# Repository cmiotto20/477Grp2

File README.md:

# 477Grp2
MOUSE is a mobile surveillance robot intended for indoor use, in corporate office or residential environments. MOUSE will be powered by four motors, each controlling its own wheel for mobility. There will be a large 12V battery allowing MOUSE to perform surveillance overnight without needing to have its battery replaced. When the battery does die, it will need to be recharged manually. MOUSE will have the ability for the motors to have variable speed control through the use of PWM signals. MOUSE will also have a custom circuit to step down the 12V from the battery to 5V for motors, sensors and ICs, aswell as 5V to 3.3V for the microprocessor.

To complete its surveillance functionality, MOUSE will have ultrasonic sensors on all four sides, allowing for the detection of movement. While stationary, MOUSE will use these sensors to detect any movement in its vicinity. Finally, there will be a viewable UI on a webpage to use MOUSE movement controls and display if any objects have been detected. MOUSE and the web interface will send data wirelessly through WiFi via a web server. The block diagram below represents the connections between the described functional components of MOUSE.

Additionally, we have the following stretch goals for the functionality of MOUSE. Mouse may have a series of LEDs which will be used to display diagnostics such as battery life. There may be an ability to measure data from a lidar sensor to provide redundancy and confirm the readings from the ultrasonic sensors. Finally, MOUSE may be able to follow a predetermined path set by the user.

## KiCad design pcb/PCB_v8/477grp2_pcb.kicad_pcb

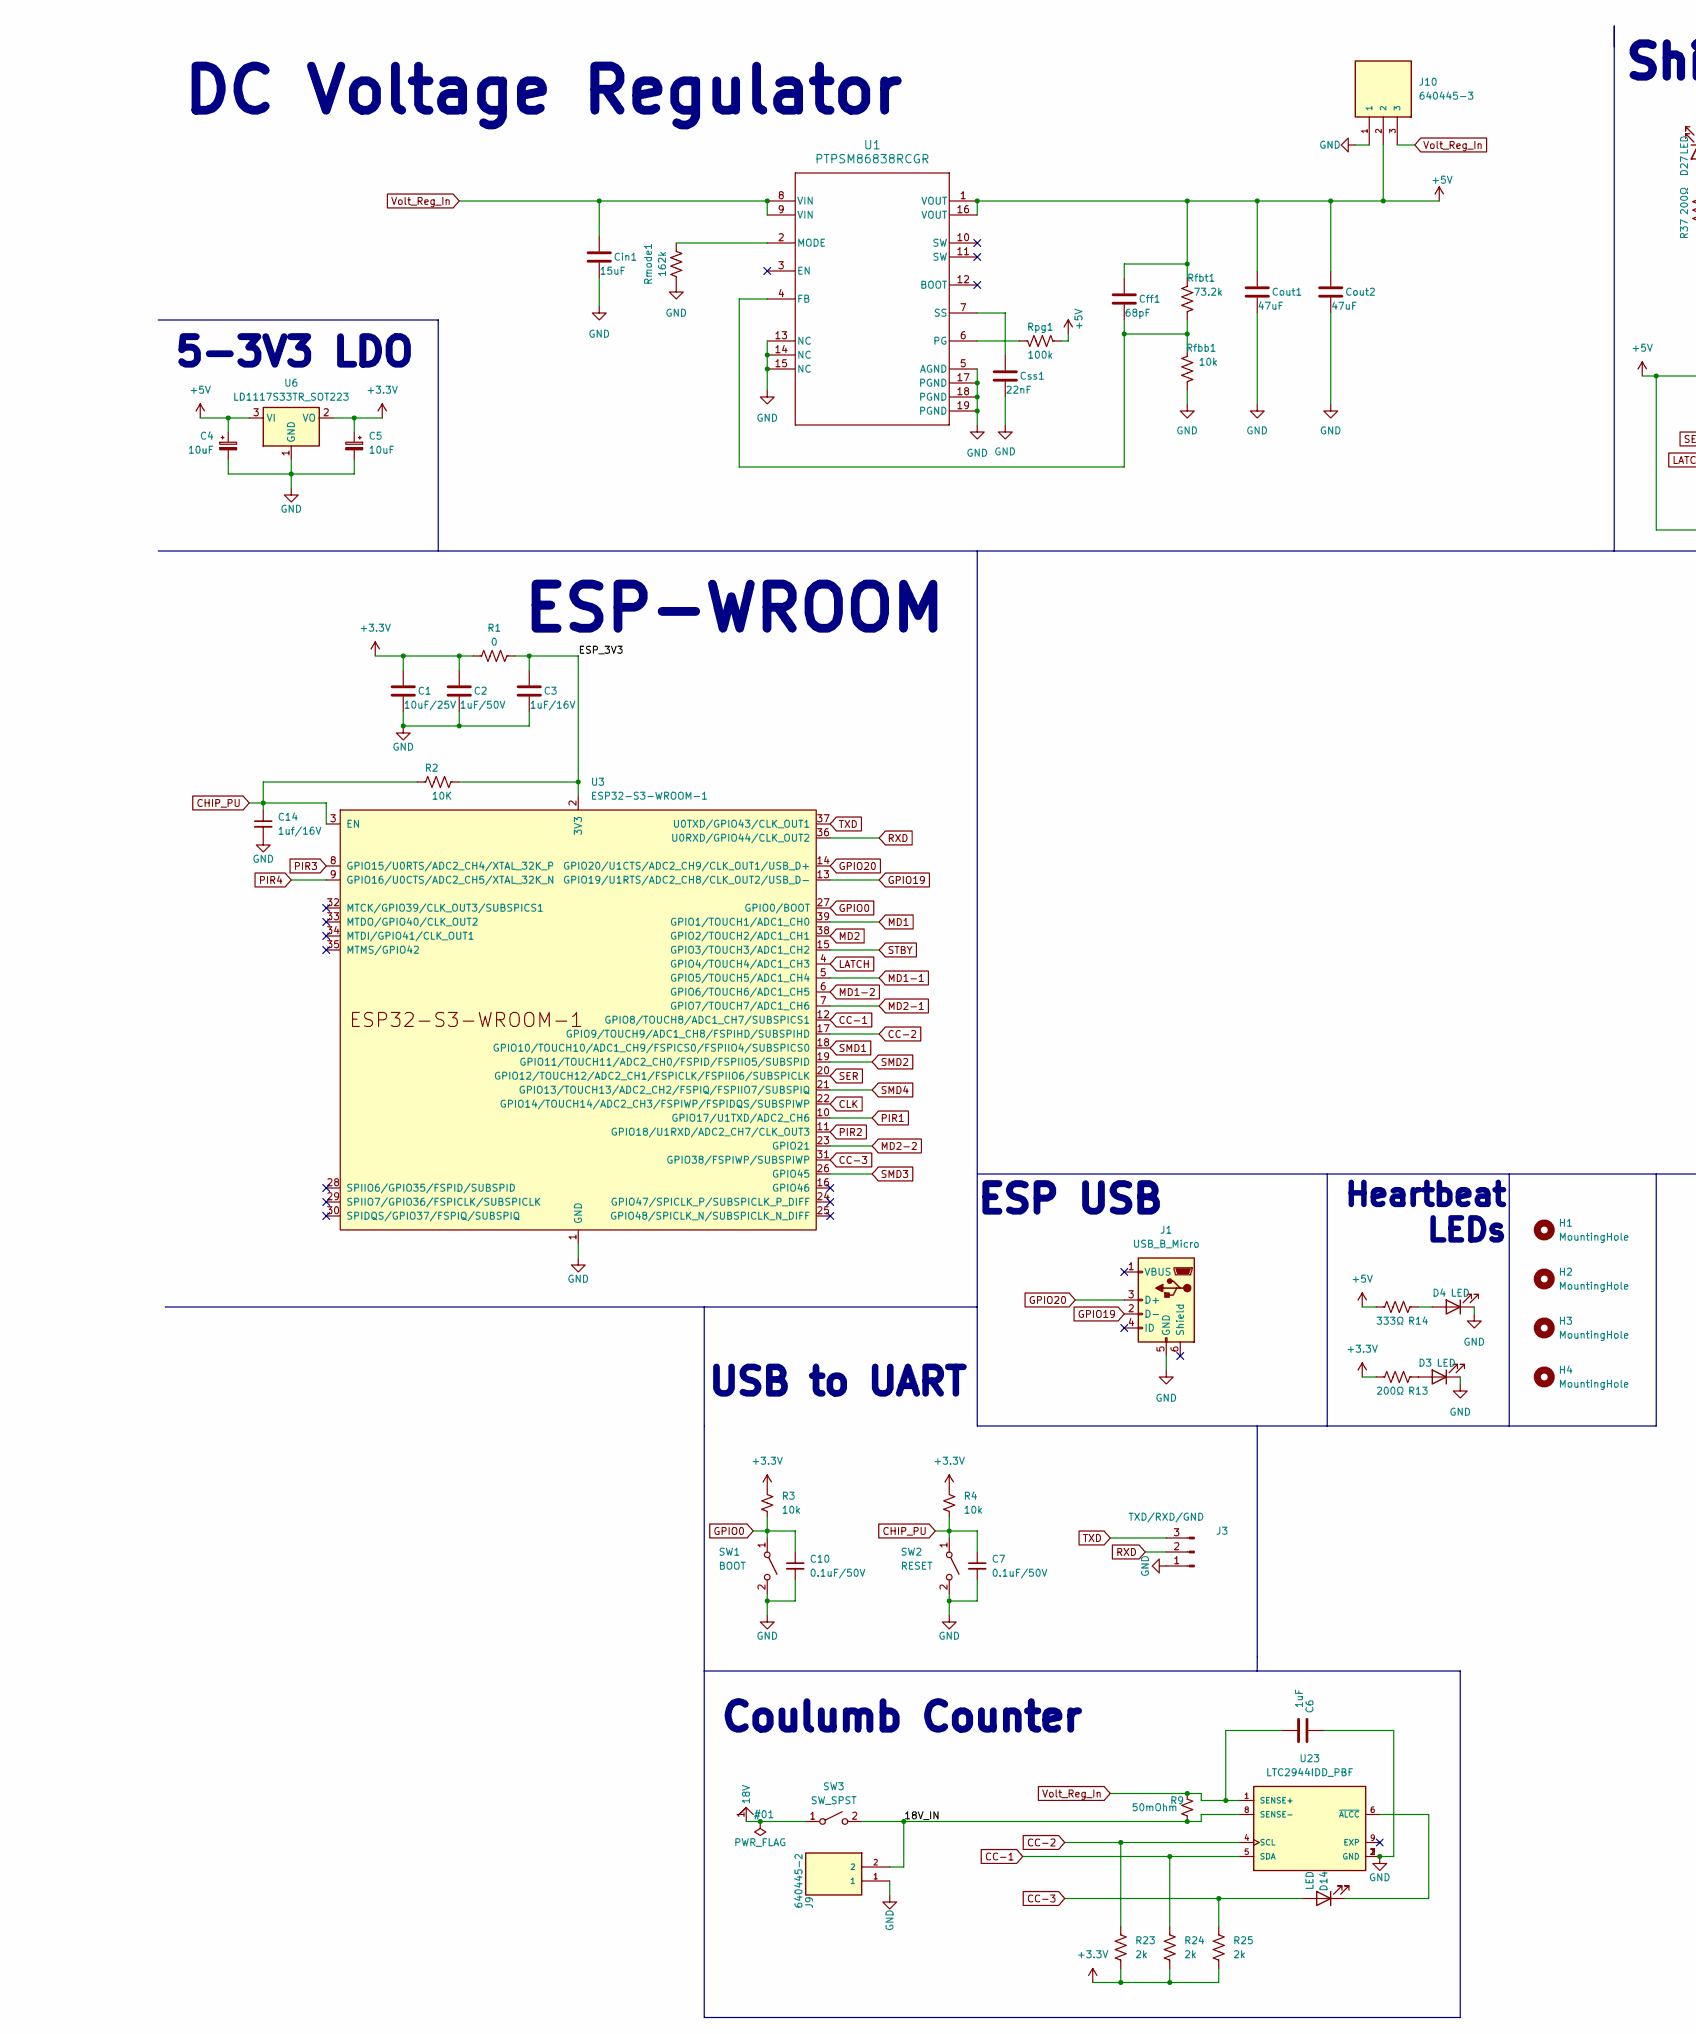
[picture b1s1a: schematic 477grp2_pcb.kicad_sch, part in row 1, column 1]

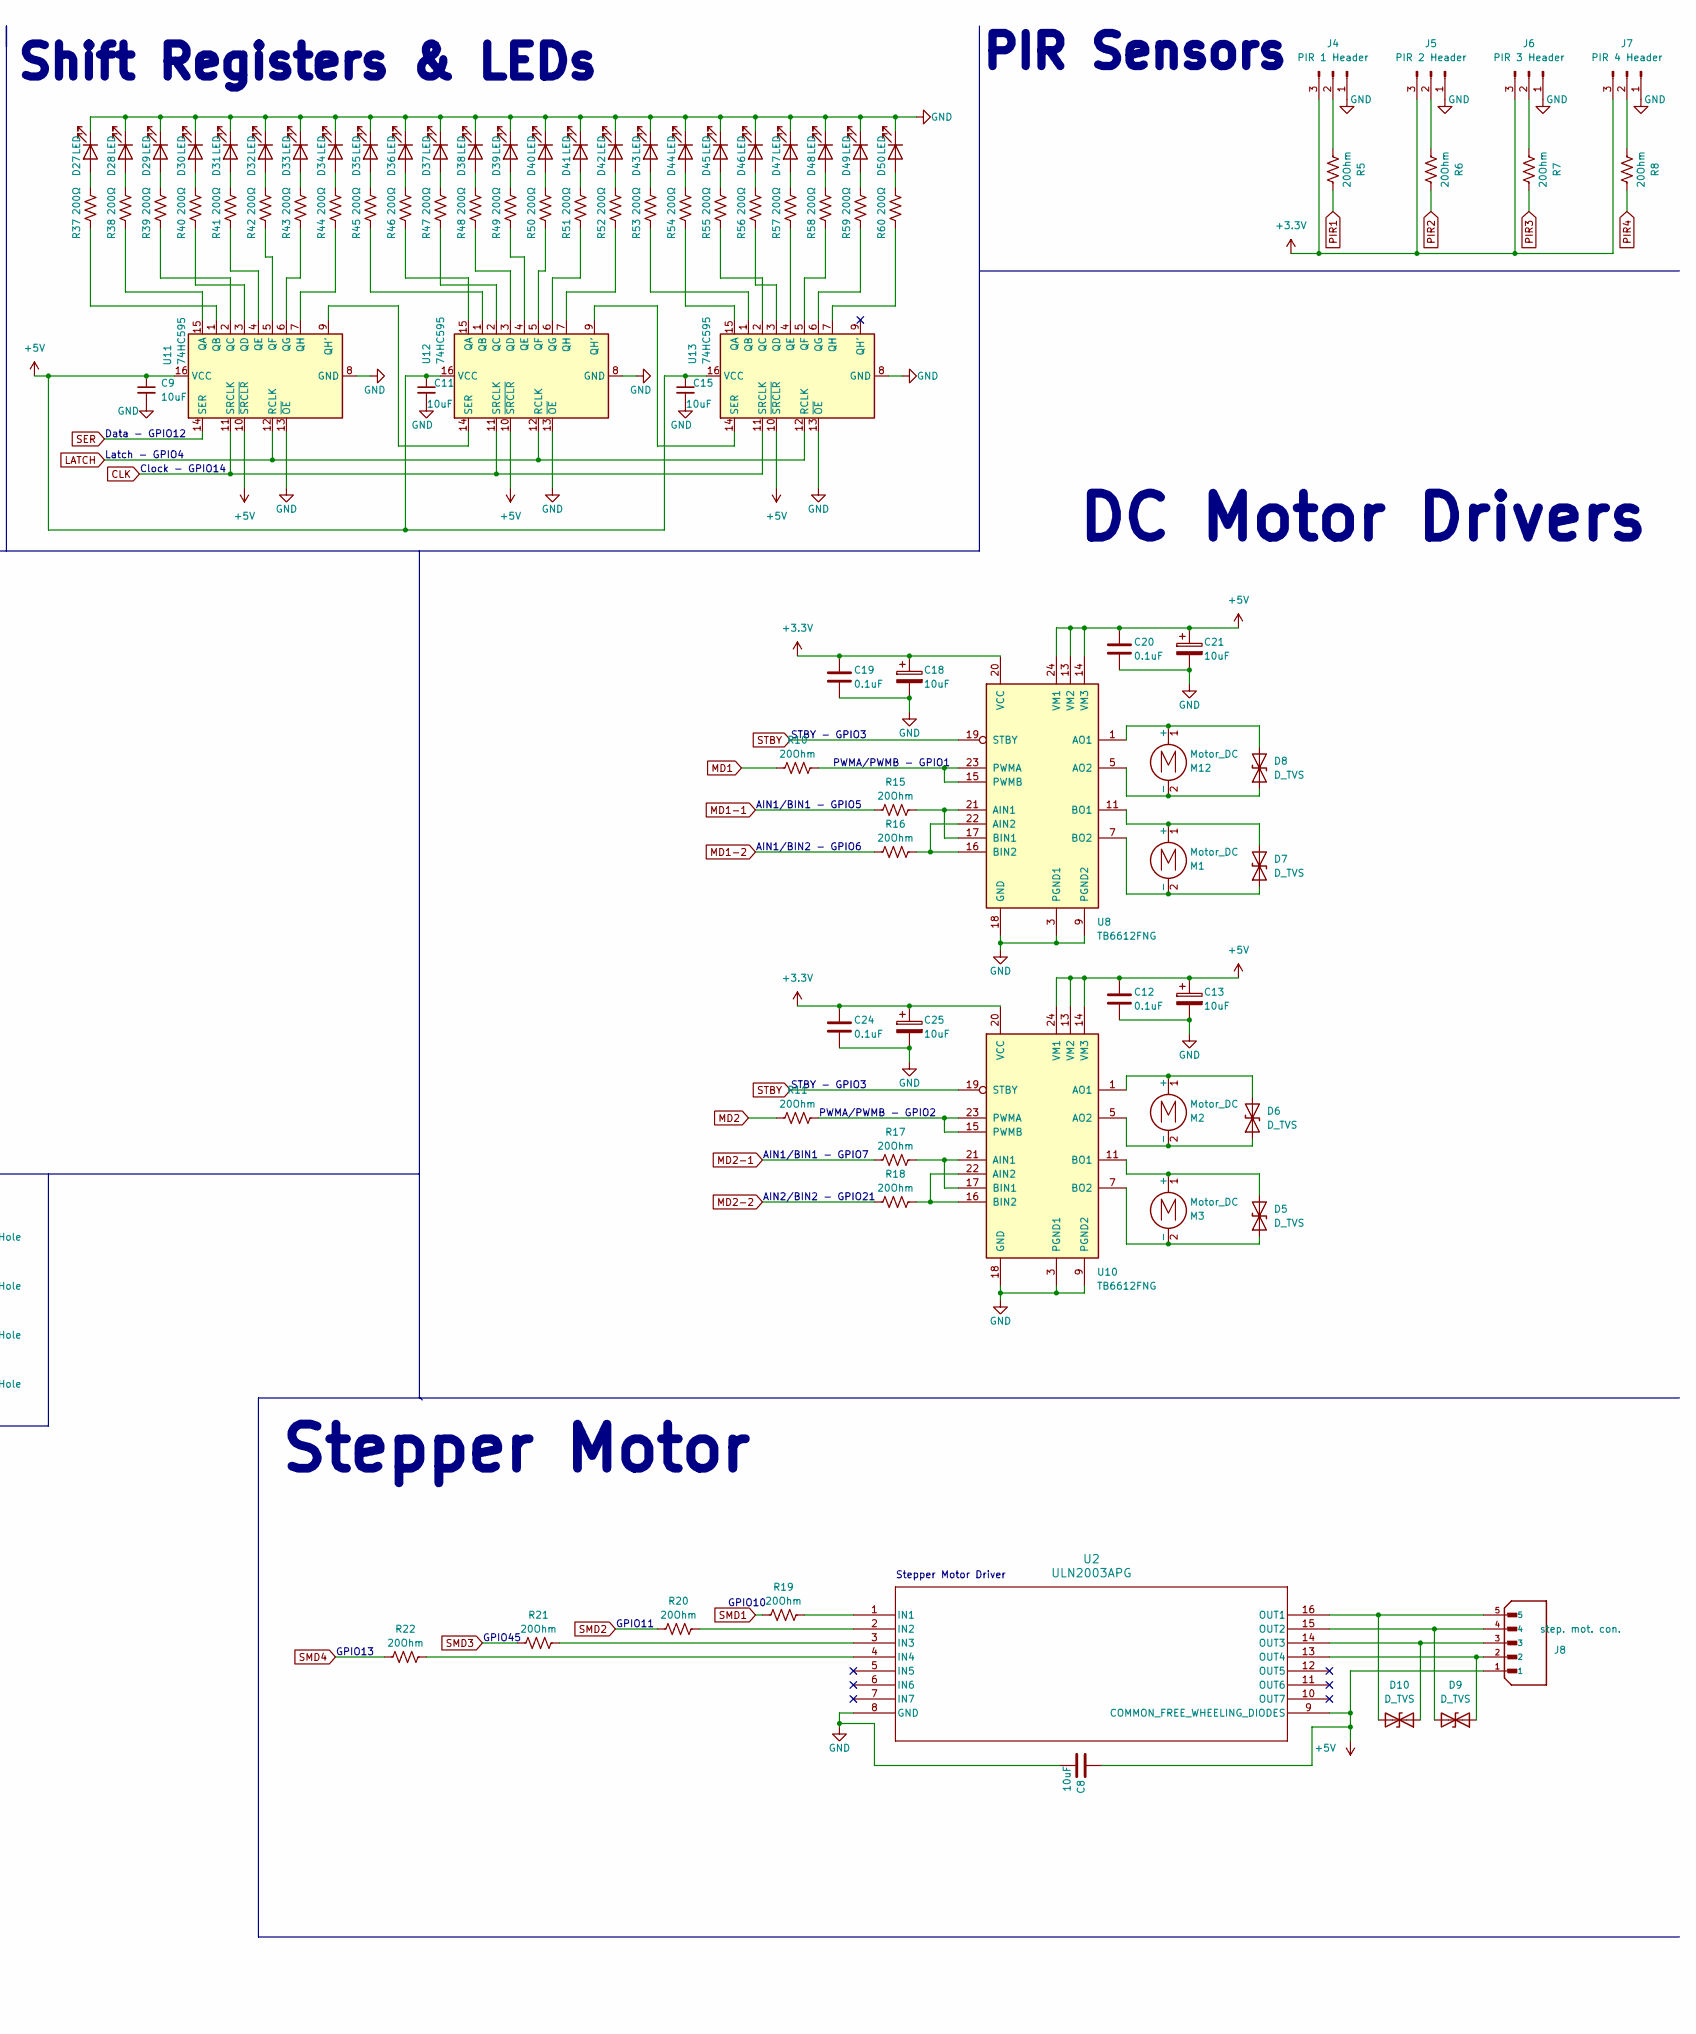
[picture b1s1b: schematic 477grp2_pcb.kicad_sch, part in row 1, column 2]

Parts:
C1: 10uF/25V; C_0805_2012Metric
C2: 1uF/50V; C_0805_2012Metric
C3: 1uF/16V; C_0805_2012Metric
C4, C5, C8: 10uF; C_0805_2012Metric
C6: 1uF; C_0805_2012Metric
C7, C10: 0.1uF/50V; C_0805_2012Metric
C9, C11, C15: 10uF; C_0805_2012Metric_Pad1.18x1.45mm_HandSolder
C12, C19, C20, C24: 0.1uF; C_0805_2012Metric
C13, C18, C21, C25: 10uF; CP_Elec_6.3x7.7
C14: 1uf/16V; C_0805_2012Metric
Cff1: 68pF; C_0805_2012Metric_Pad1.18x1.45mm_HandSolder
Cin1: 15uF; C_0805_2012Metric
Cout1, Cout2: 47uF; C_1206_3216Metric_Pad1.33x1.80mm_HandSolder
Css1: 22nF; C_0603_1608Metric_Pad1.08x0.95mm_HandSolder
D3, D4, D14: LED; LED_0805_2012Metric
D5, D6, D7, D8, D9, D10: D_TVS; PinHeader_1x02_P2.54mm_Vertical
D27, D28, D29, D30, D31, D32, D33, D34, D35, D36, D37, D38, D39, D40, D41, D42, D43, D44, D45, D46, D47, D48, D49, D50: LED; PinHeader_2x01_P2.54mm_Vertical
H1, H2, H3, H4: MountingHole; MountingHole_2.5mm_Pad_Via
J1: USB_B_Micro; USB_Micro-B_Molex-105017-0001
J3: TXD/RXD/GND; PinHeader_1x03_P2.54mm_Vertical
J4: PIR 1 Header; PinHeader_1x03_P2.54mm_Vertical
J5: PIR 2 Header; PinHeader_1x03_P2.54mm_Vertical
J6: PIR 3 Header; PinHeader_1x03_P2.54mm_Vertical
J7: PIR 4 Header; PinHeader_1x03_P2.54mm_Vertical
J8: step. mot. con.; PinHeader_1x05_P2.54mm_Vertical; PARTREV 7/4/21
J9: 640445-2; MTA_156; PARTREV R
J10: 640445-3; TE_640445-3; PARTREV R
M1, M2, M3, M12: Motor_DC; JST_VH_B2P-VH_1x02_P3.96mm_Vertical
R1: 0; R_0805_2012Metric_Pad1.20x1.40mm_HandSolder
R2: 10K; R_0805_2012Metric_Pad1.20x1.40mm_HandSolder
R3, R4: 10k; R_0805_2012Metric
R5, R6, R7, R8, R10, R11, R15, R16, R17, R18, R19, R20, R21, R22: 20Ohm; R_0805_2012Metric_Pad1.20x1.40mm_HandSolder
R9: 50mOhm; R_2512_6332Metric_Pad1.40x3.35mm_HandSolder
R13, R37, R38, R39, R40, R41, R42, R43, R44, R45, R46, R47, R48, R49, R50, R51, R52, R53, R54, R55, R56, R57, R58, R59, R60: 200Ω; R_0805_2012Metric_Pad1.20x1.40mm_HandSolder
R14: 333Ω; R_0805_2012Metric_Pad1.20x1.40mm_HandSolder
R23, R24, R25: 2k; R_0805_2012Metric_Pad1.20x1.40mm_HandSolder
Rfbb1: 10k; R_0603_1608Metric_Pad0.98x0.95mm_HandSolder
Rfbt1: 73.2k; R_0603_1608Metric_Pad0.98x0.95mm_HandSolder
Rmode1: 162k; R_0603_1608Metric_Pad0.98x0.95mm_HandSolder
Rpg1: 100k; R_0805_2012Metric_Pad1.20x1.40mm_HandSolder
SW1: BOOT; SW_SPST_B3S-1000
SW2: RESET; SW_SPST_B3S-1000
SW3: SW_SPST
U1: PTPSM86838RCGR; RCG0019A-MFG
U2: ULN2003APG; DIP-16L_6P35X19P18_TOS
U3: ESP32-S3-WROOM-1
U6: LD1117S33TR_SOT223; SOT-223-3_TabPin2
U8, U10: TB6612FNG; SSOP-24_5.3x8.2mm_P0.65mm
U11, U12, U13: 74HC595; NS16
U23: LTC2944IDD_PBF; SON300X300X80-9N

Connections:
+3.3V: C1.1, C2.1, C5.1, C18.1, C19.1, C24.1, C25.1, J4.3, J5.3, J6.3, J7.3, R1.1, R3.1, R4.1, R13.2, R23.2, R24.2, R25.2, U6.2 (VO), U8.20 (VCC), U10.20 (VCC)
+5V: C4.1, C8.1, C9.1, C11.1, C12.1, C13.1, C15.1, C20.1, C21.1, Cff1.1, Cout1.1, Cout2.1, J8.1, J10.2, R14.2, Rfbt1.1, Rpg1.1, U1.1 (VOUT), U1.16 (VOUT), U2.9 (COMMON_FREE_WHEELING_DIODES), U6.3 (VI), U8.13 (VM2), U8.14 (VM3), U8.24 (VM1), U10.13 (VM2), U10.14 (VM3), U10.24 (VM1), U11.10 (~SRCLR), U11.16 (VCC), U12.10 (~SRCLR), U12.16 (VCC), U13.10 (~SRCLR), U13.16 (VCC)
/18V_IN: J9.2, R9.2, SW3.2 (B), U23.8 (SENSE-)
/ESP_3V3: C3.1, R1.2, R2.1, U3.2 (3V3)
CC-1: R24.1, U3.12 (GPIO8/TOUCH8/ADC1_CH7/SUBSPICS1), U23.5 (SDA)
CC-2: R23.1, U3.17 (GPIO9/TOUCH9/ADC1_CH8/FSPIHD/SUBSPIHD), U23.4 (SCL)
CC-3: D14.2 (A), R25.1, U3.31 (GPIO38/FSPIWP/SUBSPIWP)
CHIP_PU: C7.1, C14.1, R2.2, R4.2, SW2.1 (A), U3.3 (EN)
CLK: U3.22 (GPIO14/TOUCH14/ADC2_CH3/FSPIWP/FSPIDQS/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), U11.11 (SRCLK), U12.11 (SRCLK), U13.11 (SRCLK)
GND: C1.2, C2.2, C3.2, C4.2, C5.2, C6.1, C7.2, C8.2, C9.2, C10.2, C11.2, C12.2, C13.2, C14.2, C15.2, C18.2, C19.2, C20.2, C21.2, C24.2, C25.2, Cin1.2, Cout1.2, Cout2.2, Css1.2, D3.1 (K), D4.1 (K), D27.1 (K), D28.1 (K), D29.1 (K), D30.1 (K), D31.1 (K), D32.1 (K), D33.1 (K), D34.1 (K), D35.1 (K), D36.1 (K), D37.1 (K), D38.1 (K), D39.1 (K), D40.1 (K), D41.1 (K), D42.1 (K), D43.1 (K), D44.1 (K), D45.1 (K), D46.1 (K), D47.1 (K), D48.1 (K), D49.1 (K), D50.1 (K), J1.5 (GND), J3.1, J4.1, J5.1, J6.1, J7.1, J9.1, J10.1, Rfbb1.2, Rmode1.1, SW1.2 (B), SW2.2 (B), U1.5 (AGND), U1.13 (NC), U1.14 (NC), U1.15 (NC), U1.17 (PGND), U1.18 (PGND), U1.19 (PGND), U2.8 (GND), U3.1 (GND), U3.40 (GND), U3.41 (GND), U6.1 (GND), U8.3 (PGND1), U8.4 (PGND1), U8.9 (PGND2), U8.10 (PGND2), U8.18 (GND), U10.3 (PGND1), U10.4 (PGND1), U10.9 (PGND2), U10.10 (PGND2), U10.18 (GND), U11.8 (GND), U11.13 (~OE), U12.8 (GND), U12.13 (~OE), U13.8 (GND), U13.13 (~OE), U23.2 (GND), U23.3 (GND), U23.7 (GND)
GPIO0: C10.1, R3.2, SW1.1 (A), U3.27 (GPIO0/BOOT)
GPIO19: J1.2 (D-), U3.13 (GPIO19/U1RTS/ADC2_CH8/CLK_OUT2/USB_D-)
GPIO20: J1.3 (D+), U3.14 (GPIO20/U1CTS/ADC2_CH9/CLK_OUT1/USB_D+)
LATCH: U3.4 (GPIO4/TOUCH4/ADC1_CH3), U11.12 (RCLK), U12.12 (RCLK), U13.12 (RCLK)
MD1: R10.1, U3.39 (GPIO1/TOUCH1/ADC1_CH0)
MD1-1: R15.1, U3.5 (GPIO5/TOUCH5/ADC1_CH4)
MD1-2: R16.1, U3.6 (GPIO6/TOUCH6/ADC1_CH5)
MD2: R11.1, U3.38 (GPIO2/TOUCH2/ADC1_CH1)
MD2-1: R17.1, U3.7 (GPIO7/TOUCH7/ADC1_CH6)
MD2-2: R18.1, U3.23 (GPIO21)
unnamed: D3.2 (A), R13.1
unnamed: D4.2 (A), R14.1
unnamed: D5.1 (A1), M3.2 (-), U10.7 (BO2), U10.8 (BO2)
unnamed: D5.2 (A2), M3.1 (+), U10.11 (BO1), U10.12 (BO1)
unnamed: D6.1 (A1), M2.2 (-), U10.5 (AO2), U10.6 (AO2)
unnamed: D6.2 (A2), M2.1 (+), U10.1 (AO1), U10.2 (AO1)
unnamed: D7.1 (A1), M1.2 (-), U8.7 (BO2), U8.8 (BO2)
unnamed: D7.2 (A2), M1.1 (+), U8.11 (BO1), U8.12 (BO1)
unnamed: D8.1 (A1), M12.2 (-), U8.5 (AO2), U8.6 (AO2)
unnamed: D8.2 (A2), M12.1 (+), U8.1 (AO1), U8.2 (AO1)
unnamed: D9.1 (A1), J8.2, U2.13 (OUT4)
unnamed: D9.2 (A2), J8.4, U2.15 (OUT2)
unnamed: D10.1 (A1), J8.3, U2.14 (OUT3)
unnamed: D10.2 (A2), J8.5, U2.16 (OUT1)
unnamed: D14.1 (K), U23.6 (~ALCC)
unnamed: D27.2 (A), R37.2
unnamed: D28.2 (A), R38.2
unnamed: D29.2 (A), R39.2
unnamed: D30.2 (A), R40.2
unnamed: D31.2 (A), R41.2
unnamed: D32.2 (A), R42.2
unnamed: D33.2 (A), R43.2
unnamed: D34.2 (A), R44.2
unnamed: D35.2 (A), R45.2
unnamed: D36.2 (A), R46.2
unnamed: D37.2 (A), R47.2
unnamed: D38.2 (A), R48.2
unnamed: D39.2 (A), R49.2
unnamed: D40.2 (A), R50.2
unnamed: D41.2 (A), R51.2
unnamed: D42.2 (A), R52.2
unnamed: D43.2 (A), R53.2
unnamed: D44.2 (A), R54.2
unnamed: D45.2 (A), R55.2
unnamed: D46.2 (A), R56.2
unnamed: D47.2 (A), R57.2
unnamed: D48.2 (A), R58.2
unnamed: D49.2 (A), R59.2
unnamed: D50.2 (A), R60.2
unnamed: J4.2, R5.1
unnamed: J5.2, R6.1
unnamed: J6.2, R7.1
unnamed: J7.2, R8.1
unnamed: Cff1.2, Rfbb1.1, Rfbt1.2, U1.4 (FB)
unnamed: Rmode1.2, U1.2 (MODE)
unnamed: Rpg1.2, U1.6 (PG)
unnamed: Css1.1, U1.7 (SS)
unnamed: R19.2, U2.1 (IN1)
unnamed: R20.2, U2.2 (IN2)
unnamed: R21.2, U2.3 (IN3)
unnamed: R22.2, U2.4 (IN4)
unnamed: R15.2, U8.17 (BIN1), U8.21 (AIN1)
unnamed: R16.2, U8.16 (BIN2), U8.22 (AIN2)
unnamed: R10.2, U8.15 (PWMB), U8.23 (PWMA)
unnamed: R17.2, U10.17 (BIN1), U10.21 (AIN1)
unnamed: R18.2, U10.16 (BIN2), U10.22 (AIN2)
unnamed: R11.2, U10.15 (PWMB), U10.23 (PWMA)
unnamed: R38.1, U11.15 (QA)
unnamed: R37.1, U11.1 (QB)
unnamed: R39.1, U11.2 (QC)
unnamed: R40.1, U11.3 (QD)
unnamed: R41.1, U11.4 (QE)
unnamed: R42.1, U11.5 (QF)
unnamed: R43.1, U11.6 (QG)
unnamed: U11.9 (QH'), U12.14 (SER)
unnamed: R44.1, U11.7 (QH)
unnamed: R46.1, U12.15 (QA)
unnamed: R45.1, U12.1 (QB)
unnamed: R47.1, U12.2 (QC)
unnamed: R48.1, U12.3 (QD)
unnamed: R49.1, U12.4 (QE)
unnamed: R50.1, U12.5 (QF)
unnamed: R51.1, U12.6 (QG)
unnamed: U12.9 (QH'), U13.14 (SER)
unnamed: R52.1, U12.7 (QH)
unnamed: R54.1, U13.15 (QA)
unnamed: R53.1, U13.1 (QB)
unnamed: R55.1, U13.2 (QC)
unnamed: R56.1, U13.3 (QD)
unnamed: R57.1, U13.4 (QE)
unnamed: R58.1, U13.5 (QF)
unnamed: R59.1, U13.6 (QG)
unnamed: R60.1, U13.7 (QH)
PIR1: R5.2, U3.10 (GPIO17/U1TXD/ADC2_CH6)
PIR2: R6.2, U3.11 (GPIO18/U1RXD/ADC2_CH7/CLK_OUT3)
PIR3: R7.2, U3.8 (GPIO15/U0RTS/ADC2_CH4/XTAL_32K_P)
PIR4: R8.2, U3.9 (GPIO16/U0CTS/ADC2_CH5/XTAL_32K_N)
RXD: J3.2, U3.36 (U0RXD/GPIO44/CLK_OUT2)
SER: U3.20 (GPIO12/TOUCH12/ADC2_CH1/FSPICLK/FSPIIO6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), U11.14 (SER)
SMD1: R19.1, U3.18 (GPIO10/TOUCH10/ADC1_CH9/FSPICS0/FSPIIO4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)
SMD2: R20.1, U3.19 (GPIO11/TOUCH11/ADC2_CH0/FSPID/FSPIIO5/S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)
SMD3: R21.1, U3.26 (GPIO45)
SMD4: R22.1, U3.21 (GPIO13/TOUCH13/ADC2_CH2/FSPIQ/FSPIIO7/S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)
STBY: U3.15 (GPIO3/TOUCH3/ADC1_CH2), U8.19 (STBY), U10.19 (STBY)
TXD: J3.3, U3.37 (U0TXD/GPIO43/CLK_OUT1)
Volt_Reg_In: C6.2, Cin1.1, J10.3, R9.1, U1.8 (VIN), U1.9 (VIN), U23.1 (SENSE+)

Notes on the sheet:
ESP-WROOM
GPIO11
PWMA/PWMB - GPIO2
Shift Registers & LEDs
PWMA/PWMB - GPIO1
Clock - GPIO14
DC Voltage Regulator
Heartbeat LEDs
GPIO45
5-3V3 LDO
Latch - GPIO4
AIN2/BIN2 - GPIO21
Stepper Motor
Stepper Motor Driver
GPIO10
AIN1/BIN1 - GPIO5
STBY - GPIO3
AIN1/BIN1 - GPIO7
AIN1/BIN2 - GPIO6
GPIO13
ESP USB
DC Motor Drivers
USB to UART
Data - GPIO12
Coulumb Counter
PIR Sensors

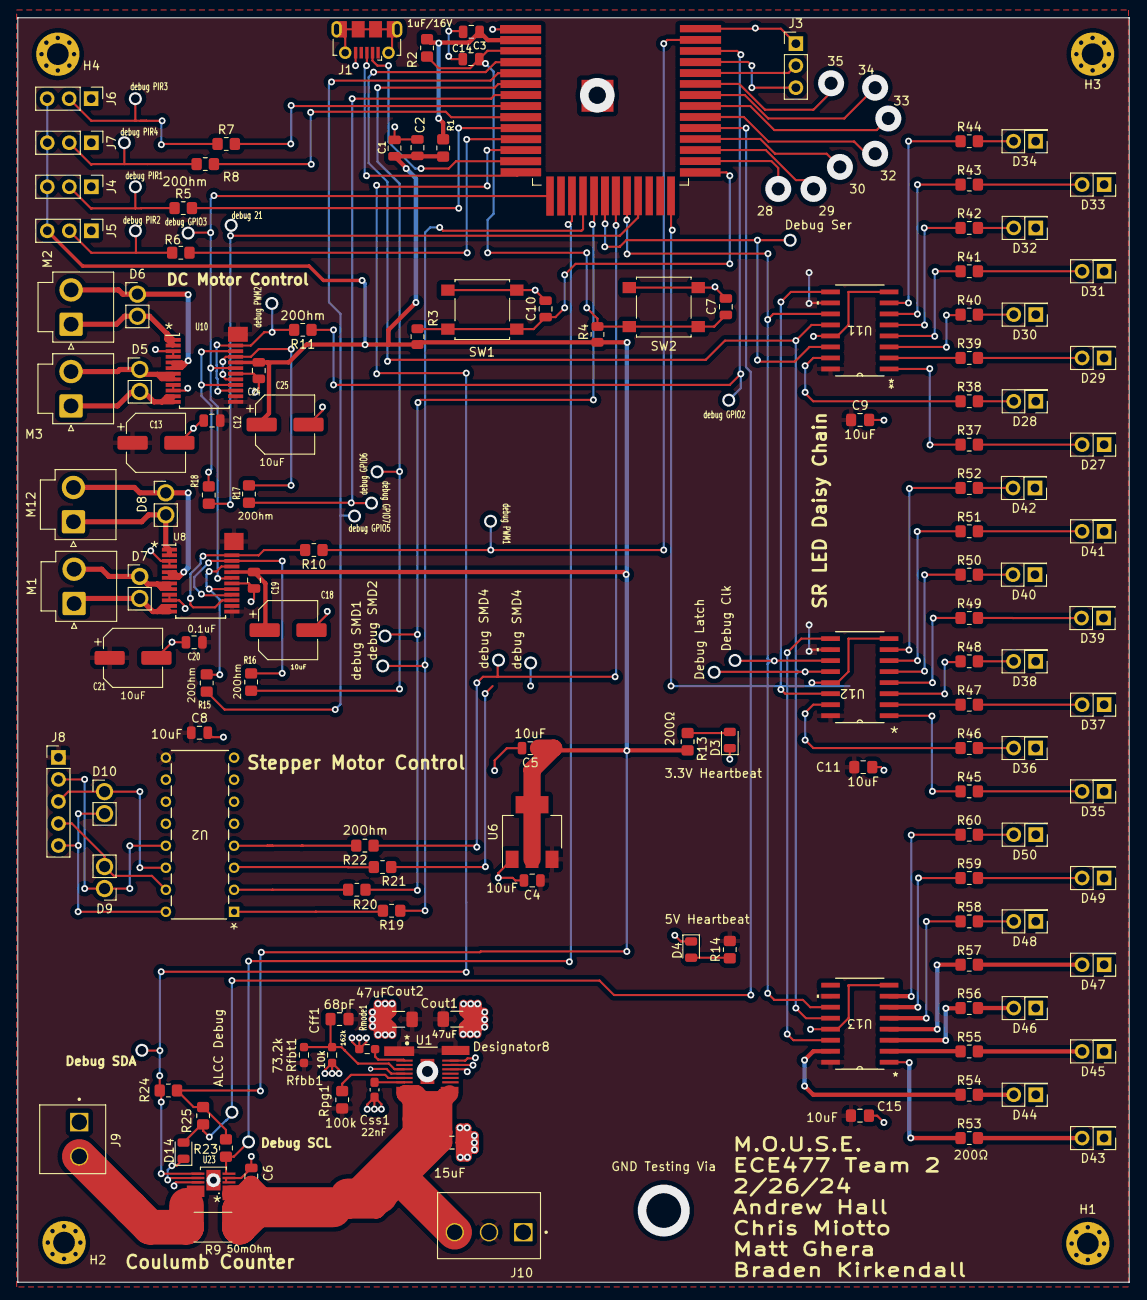
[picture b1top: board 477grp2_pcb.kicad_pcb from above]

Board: 2 copper layers, 128.2 x 145.9 mm, 140 parts (0 on the bottom side), 116 nets.

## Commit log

2024-01-14 added simple api endpoint for esp to test with
2024-01-14 added http call from ESP to api test code
2024-01-15 added simple VUE web UI that calls api endpoint
2024-01-15 updated ip for API call
2024-01-15 added dist for Vue
2024-01-15 updated ip for api
2024-01-15 added toggle light api endpoint
2024-01-15 fixed bug in toggleLight api endpoint
2024-01-15 added getLightVal api endpoint
2024-01-15 updated getLedVal api endpoint to return different string
2024-01-15 updated getLightVal api endpoint
2024-01-15 debugging toggleLight api endpoint
2024-01-16 updated ip
2024-01-16 added static ip addr
2024-01-16 added static ip to mainPage
2024-01-18 added button components for directional movement
2024-01-19 adding endpoints for directional traversal
2024-01-20 ip update
2024-01-20 lowered delays for http req
2024-01-20 turned api into websocket and updated frontend to send to websocket
2024-01-20 built last commit
2024-01-20 converted api into webhook for backend and frontend
2024-01-21 updated web socket for microcontroller
2024-01-21 updated get light status endpoint
2024-01-21 added wifi connection and more modifications to websocket calls
2024-01-21 NO MORE 8 SECOND LAG
2024-01-22 PCB for leds and ESP
2024-01-22 PCBv2 with stepdown added
2024-01-22 other pcb stuff
2024-01-23 socket connections
2024-01-23 insane update to pcb
2024-01-24 implemented socket command parsing and multi-client alarming
2024-01-24 changed web ip
2024-01-24 updated websocket names for micro
2024-01-24 showing micro connection
2024-01-24 checking micro connection status
2024-01-24 fixed var scope
2024-01-24 frontend build
2024-01-24 updated micro connection status
2024-01-24 changed micro status update
2024-01-24 new build
2024-01-24 made micro_conn an array
2024-01-24 sensing micro logic
2024-01-25 added delay before connecting
2024-01-25 updated ui with css
2024-01-26 simplified connection check
2024-01-28 added in checking for micro connection call
2024-01-28 modified toggleLED to toggleRow for modularity
2024-01-28 debugging toggleRow
2024-01-28 modified getLEDStatus to getRowStatus to allow for modularity
2024-01-28 added file support for micro status
2024-01-28 client length bug fix
2024-01-28 micro status bug fix
2024-01-28 make micro connection rely on time
2024-01-28 make micro connection rely on time debugging 1
2024-01-28 make micro connection rely on time debugging 2
2024-01-28 css changes
2024-01-29 updated endpoints for motor contro
2024-01-29 updated motor websocket in frontend
2024-01-29 updated motor websocket
2024-01-29 added speed to websocket motor endpoint
2024-01-29 websocket speed debug
2024-01-29 websocket speed debug 2
2024-01-29 websocket speed debug 3
2024-01-29 websocket speed debug 4
2024-01-29 new css
2024-01-30 motor drivers and sonar
2024-01-30 added frontend display for message box
2024-01-30 button update
2024-01-30 merged braden and I's masterpieces
2024-01-31 added more message box frontend
2024-01-31 updated time error and alert msg
2024-01-31 uncommented localhost server
2024-01-31 added playback features
2024-02-02 pcb things
2024-02-03 added i2c sonar communication
2024-02-03 looping playback
2024-02-04 added initial sonar ws
2024-02-04 fixed bug with sonar sensor ws and added micro code to send sonar data
2024-02-04 sonar ws bugfix
2024-02-04 updated sonar ws to save to file in arr of 20
2024-02-04 added sonar ws frontend code
2024-02-04 update ip
2024-02-04 bug fix for sonar detect ws
2024-02-04 added button effects on click
2024-02-04 added btn effects on click
2024-02-05 added LDO to circuit
2024-02-05 changed sonar to 5v from 3.3
2024-02-05 button indicator of recording/playback
2024-02-05 added USB to UART and USB ESP
2024-02-07 pcb stuff
2024-02-07 Finished USB to UART
2024-02-07 More PCB
2024-02-08 power step down circuit
2024-02-09 micro code for the stepper
2024-02-10 updated sonar ws to motion detection and added state
2024-02-10 fixed motion detection display bug
2024-02-10 added stop button to frontend ws and micro
2024-02-10 added ws code to add data to mmovement logs and clear
2024-02-10 fixed currentTime bug
2024-02-10 bug fix for clearing movementlog
2024-02-10 attempting to debug prepend data to row function
2024-02-10 attempting to debug prepend date to row function
2024-02-10 improving logging time
2024-02-10 filter out non-dates in ws
2024-02-10 attempting to debug movement detection
2024-02-10 updated frontend for detection display
2024-02-10 updated detection log display
2024-02-10 pcb update
2024-02-10 small pcb update
2024-02-13 pwm code
2024-02-13 More USB UART PCB stuff
2024-02-14 PWM demo
2024-02-14 more pcb better
2024-02-14 removed vscode config
2024-02-14 Added Headers and swithcd linear reg to ld1117
2024-02-15 pcb more better
2024-02-15 Seperated USB USART and USB ESP
2024-02-15 few more changes
2024-02-15 almost done with schematic
2024-02-15 schematic stuff
2024-02-15 more footprints
2024-02-16 More schematic
2024-02-16 Clean Schematic
2024-02-16 More schematic fixes
2024-02-16 Even more schemtic stuff
2024-02-16 Added Labels to Schematic
2024-02-16 added coulumb counter
2024-02-17 stepper motor stuff
2024-02-17 finished footprints
2024-02-17 finished assigning footprints
2024-02-17 updated caps
2024-02-17 Started PCB Placement
2024-02-18 routed shift registers
2024-02-19 stepper motor, coulumb counter sections pcb
2024-02-19 DC motor Driver and SR
2024-02-19 A lot of PCB and Schematic
2024-02-19 fixing ground
2024-02-20 new dc motor driver footprint
2024-02-21 more routing
2024-02-21 poopy micro routing
2024-02-22 A lot of routing
2024-02-22 route yuh
2024-02-22 routed coloumb and stepper
2024-02-22 routing
2024-02-24 Debugging vias for DC motors added debugging leds for coulomb counter, stepper, and pir, and combined pads under esp
2024-02-24 added pir interrupt and implemented into micro and added micro state into websocket
2024-02-24 updated apiData txt for state
2024-02-24 fixed state bug
2024-02-24 state in ui
2024-02-25 routed DC regulator on PCB
2024-02-25 most of pcb checklist done
2024-02-26 New v8 with 5V top plane and GND bottom
2024-02-26 more v8 changes
2024-02-26 new pwoer
2024-02-26 more updates
2024-02-26 fixed routing for power
2024-02-26 Added debug and fix 18V
2024-02-26 updated TVS diode pad size
2024-02-26 final checklist check
2024-02-27 all the pwm stuff
2024-02-28 small changes to pcb and schematic for various things
2024-02-28 repushing pcb
2024-02-28 got rid of cap on usb
2024-03-02 part of coulumb counter and voltage in redone
2024-03-02 added pwm for motor to antenna file
2024-03-02 Finished Coulumb Counter Change
2024-03-04 increased power route size
2024-03-04 updated R9 to 2512
2024-03-04 motor traces
2024-03-04 All of Joe feedback stuff
2024-03-04 prorbably fine
2024-03-04 fixed LEDs
2024-03-04 Update fp-info-cache
2024-03-05 joes change reccomendations
2024-03-05 fixed 18V
2024-03-05 fixed connector location for external buck
2024-03-06 changed pwm code
2024-03-06 silkscreen
2024-03-06 final changes and gerbers
2024-03-08 updates to code integration
2024-03-20 updated integrated file
2024-03-27 trying to fix integrated build
2024-03-27 fixing compilation error
2024-03-27 fixed integration
2024-03-27 added integrated code
2024-03-29 working shift register code in mcpwm file
2024-03-31 changes to PCB
2024-04-10 integrated code v2
2024-04-10 added globals for turn calibration
2024-04-14 new motor control micro code
2024-04-14 added playback status
2024-04-14 updated start playback button
2024-04-14 small
2024-04-14 updated playback
2024-04-15 playback and scan toggle
2024-04-15 fixed frontend bug in recording/playback states
2024-04-15 endpoint for scan
2024-04-15 break
2024-04-22 added allCode zip
2024-04-25 allCode fix
